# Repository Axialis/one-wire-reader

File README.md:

# One-Wire-Reader
One Wire Reader for 8 DS18B20 sensors on DS2482-100 (Maxim Integrated).
Addresses are written to non-volatile memory 

Schematic (KiCad):

Photo:

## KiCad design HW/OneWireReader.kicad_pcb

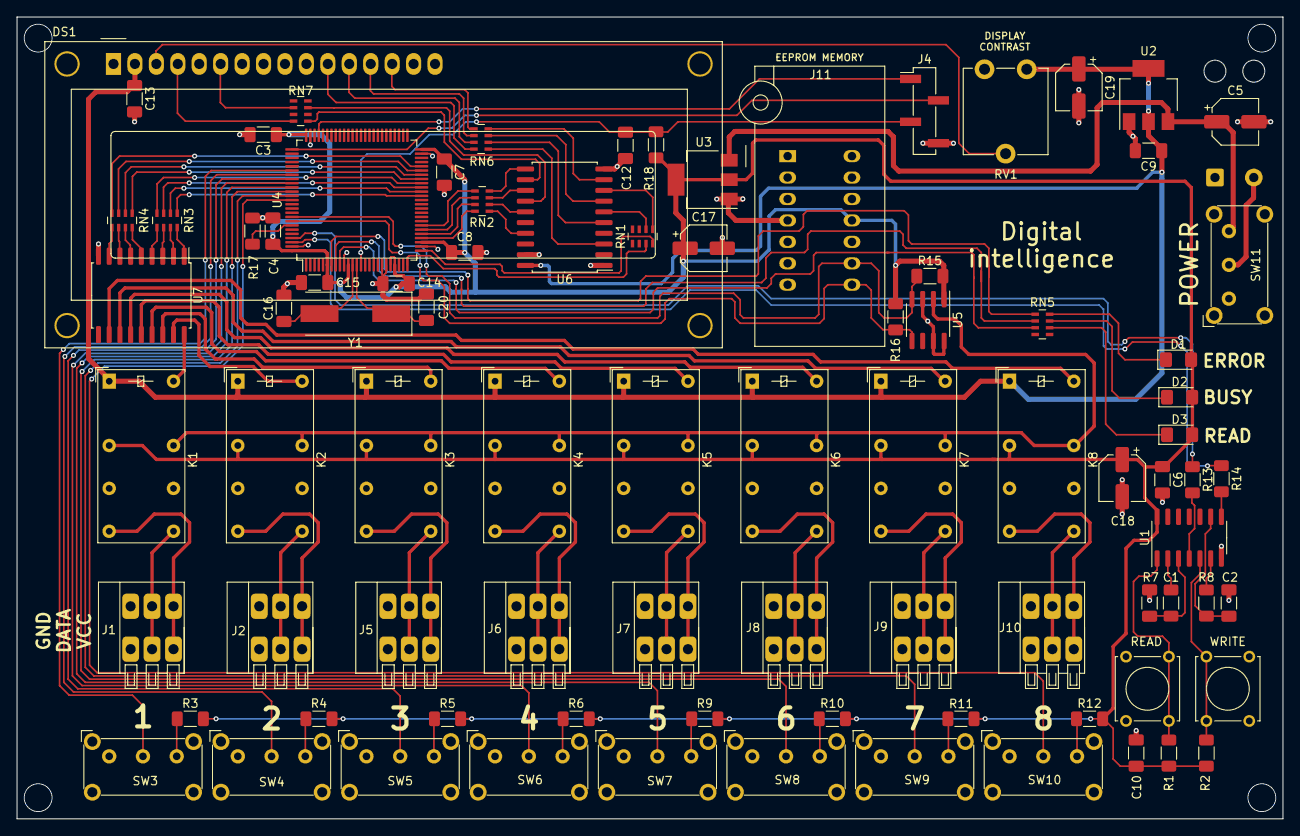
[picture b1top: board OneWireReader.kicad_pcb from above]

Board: 2 copper layers, 150.0 x 95.0 mm, 87 parts (1 on the bottom side), 111 nets.

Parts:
C1, C2, C3, C4, C6, C7, C8, C9, C10, C12, C13, C14, C15: 100n; C_1206_3216Metric_Pad1.33x1.80mm_HandSolder
C5, C17, C18, C19: 10uF x16V; CP_Elec_5x5.4
C16, C20: 22p; C_1206_3216Metric_Pad1.33x1.80mm_HandSolder
D1, D2, D3: LED; LED_1206_3216Metric_Pad1.42x1.75mm_HandSolder
DS1: WC1602A
J1, J2, J5, J6, J7, J8, J9, J10: DG141V-2.54-03P-14-00A(H)
J3: Wire; SolderWire-0.5sqmm_1x02_P4.6mm_D0.9mm_OD2.1mm_Relief
J4: Programming; PinHeader_1x04_P2.54mm_Vertical_SMD_Pin1Left
J11: ZIF-14 KLS7-SK-22H13-1-S; DIP_Socket-14_W4.3_W5.08_W7.62_W10.16_W10.9_3M_214-3339-00-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
K1, K2, K3, K4, K5, K6, K7, K8: HFD2/005-S-D(FINDER-30.22); Relay_DPDT_Finder_30.22
R1, R2, R3, R4, R5, R6, R9, R10, R11, R12, R15, R16: 4k7; R_1206_3216Metric_Pad1.30x1.75mm_HandSolder
R7, R8, R13, R14: 220; R_1206_3216Metric_Pad1.30x1.75mm_HandSolder
R17, R18: 100k; R_1206_3216Metric_Pad1.30x1.75mm_HandSolder
READ: SW_Push; SW_Tactile_Straight_KSL0Axx1LFTR
RN1, RN2, RN3, RN4, RN5, RN6, RN7: 220; R_Array_Concave_4x0603
RV1: 10k; Potentiometer_ACP_CA9-V10_Vertical
SW3, SW4, SW5, SW6, SW7, SW8, SW9, SW10, SW11: KLS7-SK-22H13-1-S; SW_E-Switch_EG1224_SPDT_Angled
U1: 74HC14; SO-14_3.9x8.65mm_P1.27mm
U2: AZ1117-5.0; SOT-223-3_TabPin2
U3: AZ1117-3.3; SOT-223-3_TabPin2
U4: STM32F105VCTx; LQFP-100_14x14mm_P0.5mm
U5: DS2482S-100; SOIC-8_3.9x4.9mm_P1.27mm
U6: 74HCT244; SOIC-20W_7.5x12.8mm_P1.27mm
U7: ULN2803A; SOIC-18W_7.5x11.6mm_P1.27mm
WRITE: SW_Push; SW_Tactile_Straight_KSL0Axx1LFTR
Y1: 8MHz; Crystal_SMD_HC49-SD

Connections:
3V3: C3.1, C4.1, C6.1, C7.1, C8.1, C10.1, C14.1, C15.1, C17.1, C18.1, D1.2, D2.2, D3.2, J11.11, K1.11, K2.11, K3.11, K4.11, K5.11, K6.11, K7.11, K8.11, R1.2, R2.2, R3.2, R4.2, R5.2, R6.2, R9.2, R10.2, R11.1, R12.2, R15.2, R16.2, R18.2, U1.14, U3.2, U4.6, U4.11, U4.21, U4.22, U4.28, U4.50, U4.75, U4.100, U5.1
5V: C9.1, C13.1, C19.1, DS1.2, K1.A1, K2.A1, K3.A1, K4.A1, K5.A1, K6.A1, K7.A1, K8.A1, RV1.3, U2.2, U6.20
/BOOT: R17.2, U4.94
/BTN_1: R13.1, U4.97
/BTN_2: R14.1, U4.98
/DS_1: RN3.1, U4.39
/DS_2: RN3.2, U4.40
/DS_3: RN3.3, U4.41
/DS_4: RN3.4, U4.42
/DS_5: RN4.1, U4.43
/DS_6: RN4.2, U4.44
/DS_7: RN4.3, U4.45
/DS_8: RN4.4, U4.46
/NRST: C12.1, J4.3, R18.1, U4.14
/OSC1: C16.1, U4.12, Y1.2
/OSC2: C20.1, U4.13, Y1.1
/OneWire: K1.21, K2.21, K3.21, K4.21, K5.21, K6.21, K7.21, K8.21, U5.2
/Rel_1: K1.A2, U7.18
/Rel_2: K2.A2, U7.17
/Rel_3: K3.A2, U7.16
/Rel_4: K4.A2, U7.15
/Rel_5: K5.A2, U7.14
/Rel_6: K6.A2, U7.13
/Rel_7: K7.A2, U7.12
/Rel_8: K8.A2, U7.11
/SCL: J11.9, R15.1, U4.92, U5.4
/SDA: J11.8, R16.1, U4.93, U5.5
/SNS_1: SW3.2, U4.81
/SNS_2: SW4.2, U4.82
/SNS_3: SW5.2, U4.83
/SNS_4: SW6.2, U4.84
/SNS_5: SW7.2, U4.85
/SNS_6: SW8.2, U4.86
/SNS_7: SW9.2, U4.87
/SNS_8: SW10.2, U4.88
/SWCLK: J4.2, U4.76
/SWDIO: J4.1, U4.72
GND: C1.1, C2.1, C3.2, C4.2, C5.2, C6.2, C7.2, C8.2, C9.2, C10.2, C12.2, C13.2, C14.2, C15.2, C16.2, C17.2, C18.2, C19.2, C20.2, DS1.1, DS1.5, J1.3, J2.3, J3.1, J4.4, J5.3, J6.3, J7.3, J8.3, J9.3, J10.3, J11.4, J11.5, J11.6, J11.7, J11.10, R17.1, READ.1, RV1.1, SW3.1, SW4.1, SW5.1, SW6.1, SW7.1, SW8.1, SW9.1, SW10.1, U1.7, U2.1, U3.1, U4.10, U4.19, U4.20, U4.27, U4.49, U4.74, U4.99, U5.3, U5.7, U5.8, U6.1, U6.10, U6.19, U7.9, WRITE.1
unnamed: C1.2, R7.1, U1.3
unnamed: C2.2, R8.1, U1.9
unnamed: C5.1, SW11.3, U2.3, U3.3
unnamed: D1.1, RN5.8
unnamed: D2.1, RN5.7
unnamed: D3.1, RN5.6
unnamed: DS1.3, RV1.2
unnamed: DS1.4, RN7.8
unnamed: DS1.6, RN7.6
unnamed: DS1.11, RN6.8
unnamed: DS1.12, RN6.7
unnamed: DS1.13, RN6.6
unnamed: DS1.14, RN6.5
unnamed: J1.1, K1.14
unnamed: J1.2, K1.24
unnamed: J2.1, K2.14
unnamed: J2.2, K2.24
unnamed: J3.2, SW11.2
unnamed: J5.1, K3.14
unnamed: J5.2, K3.24
unnamed: J6.1, K4.14
unnamed: J6.2, K4.24
unnamed: J7.1, K5.14
unnamed: J7.2, K5.24
unnamed: J8.1, K6.14
unnamed: J8.2, K6.24
unnamed: J9.1, K7.14
unnamed: J9.2, K7.24
unnamed: J10.1, K8.14
unnamed: J10.2, K8.24
unnamed: R1.1, READ.2, U1.1
unnamed: R2.1, U1.5, WRITE.2
unnamed: R3.1, SW3.3
unnamed: R4.1, SW4.3
unnamed: R5.1, SW5.3
unnamed: R6.1, SW6.3
unnamed: R7.2, U1.2
unnamed: R8.2, U1.6
unnamed: R9.1, SW7.3
unnamed: R10.1, SW8.3
unnamed: R11.2, SW9.3
unnamed: R12.1, SW10.3
unnamed: R13.2, U1.4
unnamed: R14.2, U1.8
unnamed: RN1.3, U4.25
unnamed: RN1.4, U4.26
unnamed: RN1.5, U6.8
unnamed: RN1.6, U6.6
unnamed: RN2.1, U4.32
unnamed: RN2.2, U4.31
unnamed: RN2.3, U4.30
unnamed: RN2.4, U4.29
unnamed: RN2.5, U6.17
unnamed: RN2.6, U6.15
unnamed: RN2.7, U6.13
unnamed: RN2.8, U6.11
unnamed: RN3.5, U7.4
unnamed: RN3.6, U7.3
unnamed: RN3.7, U7.2
unnamed: RN3.8, U7.1
unnamed: RN4.5, U7.8
unnamed: RN4.6, U7.7
unnamed: RN4.7, U7.6
unnamed: RN4.8, U7.5
unnamed: RN5.1, U4.7
unnamed: RN5.2, U4.8
unnamed: RN5.3, U4.9
unnamed: RN6.1, U6.3
unnamed: RN6.2, U6.5
unnamed: RN6.3, U6.7
unnamed: RN6.4, U6.9
unnamed: RN7.1, U6.12
unnamed: RN7.3, U6.14

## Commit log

2022-01-11 init: add FW reader code
2022-01-11 fix: change creator
2022-01-11 add: HW files
